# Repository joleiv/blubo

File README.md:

# BLUBO
"Blubo" is an advanced sensor for monitoring light pollution in various environments, using Hamamatsu S2386-5K photodiodes and custom transimpedance amplifiers to measure sky brightness. Essential for environmental research and crafting sustainable lighting policies.

## How to setup:

1. On a clean installation of Raspbian 11 Bullseye, install Git and download the repo:
```
git clone https://github.com/joleiv/blubo.git
```
2. After the installation is complete, you must set the file as an executable. Open terminal and run the following code:
````
cd blubo

chmod +x blubo-setup.sh

./blubo-setup.sh
````
3. Follow the instructions in the script.

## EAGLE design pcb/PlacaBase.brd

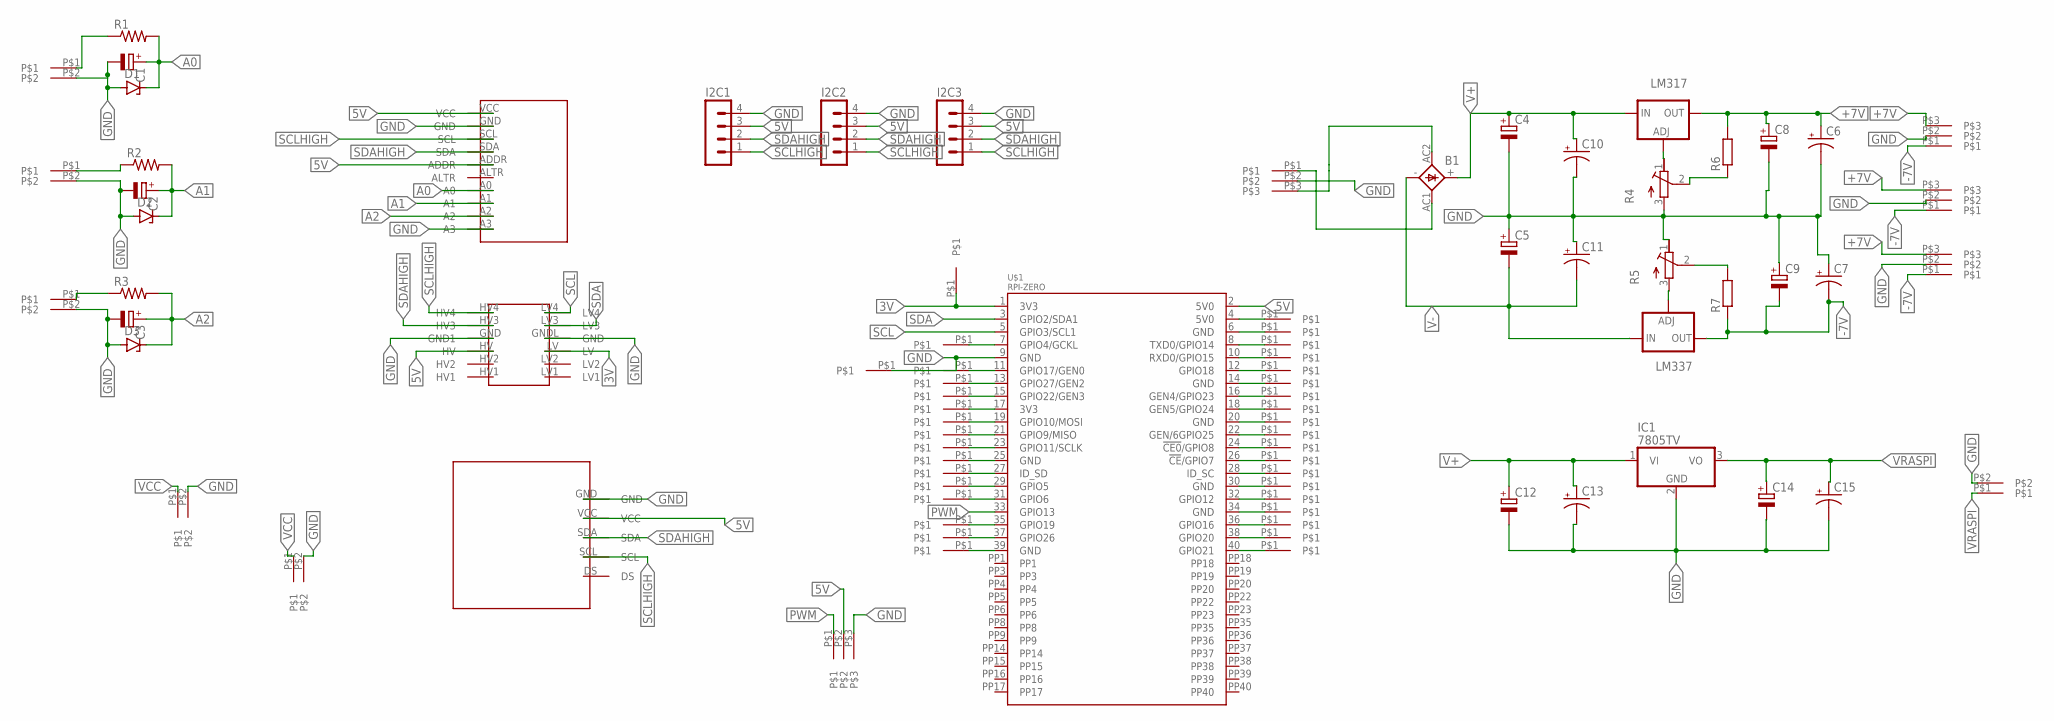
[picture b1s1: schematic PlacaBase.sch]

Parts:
5VIN: MOLEXPEQUEÑO2P
B1: KBL
C1, C2, C3: CPOL-EUE5-5; E5-5
C4, C5, C12: CPOL-EUE3.5-10; E3,5-10
C6, C7, C10, C11, C13, C15: CPOL-USTAP5-45; TAP5-45
C8, C9, C14: CPOL-EUTT2D7; TT2D7
D1, D2, D3: ZENER-DIODEDO34-7; DO34Z7
ENTRADAAC: MOLEXPEQUEÑO
I2C1, I2C2, I2C3: MA04-1
IC1: 7805TV; TO220V
LM317: LM317TS; 317TS
LM337: LM337TS; 337TS
R1, R2, R3: R-US_0204/5; 0204/5
R4, R5: R-TRIMMT93YA; RTRIMT93YA
R6, R7: R-EU_0207/7; 0207/7
U$1: RPI-ZERO; RASP_PI_ZERO_BOARD_FULL
U$2: ADS1115
U$3: RTC1307
U$4: CONVERSORLOGICO
U$5, U$13, U$14, U$15: MOLEXPEQUEÑO
U$6, U$7, U$8, U$9, U$10: MOLEXPEQUEÑO2P
U$11, U$12, U$16, U$17, U$18, U$19, U$20, U$21, U$22, U$23, U$24, U$25, U$26, U$27, U$28, U$29, U$30, U$31, U$32, U$33, U$34, U$35, U$36, U$37, U$38, U$39, U$40, U$41, U$42, U$43, U$44, U$45, U$46, U$47, U$48, U$49: PUENTE

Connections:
3V: U$1.1 (3V3), U$4.LV, U$48.P$1
3V3@2: U$1.17 (3V3), U$17.P$1
5V: I2C1.3, I2C2.3, I2C3.3, U$1.2 (5V0), U$2.ADDR, U$2.VCC, U$3.VCC, U$4.HV, U$5.P$2
5V0@2: U$1.4 (5V0), U$46.P$1
+7V: C6.+, C8.+, LM317.2 (OUT), R6.2, U$13.P$3, U$14.P$3, U$15.P$3
-7V: C7.-, C9.-, LM337.3 (OUT), R7.1, U$13.P$1, U$14.P$1, U$15.P$1
A0: C1.+, D1.C, R1.2, U$2.A0
A1: C2.+, D2.C, R2.2, U$2.A1
A2: C3.+, D3.C, R3.2, U$2.A2
AC1: B1.AC1 (AC2), ENTRADAAC.P$1
AC2: B1.AC2 (AC1), ENTRADAAC.P$3
GND: 5VIN.P$2, C1.-, C2.-, C3.-, C4.-, C5.+, C6.-, C7.+, C8.-, C9.+, C10.-, C11.+, C12.-, C13.-, C14.-, C15.-, D1.A, D2.A, D3.A, ENTRADAAC.P$2, I2C1.4, I2C2.4, I2C3.4, IC1.2 (GND), R4.3 (A), R5.1 (E), U$1.9 (GND), U$2.A3, U$2.GND, U$3.GND, U$4.GND (GND1), U$4.GNDL (GND), U$5.P$3, U$6.P$2, U$7.P$2, U$8.P$2, U$9.P$2, U$10.P$2, U$13.P$2, U$14.P$2, U$15.P$2, U$49.P$1
GND@2: U$1.25 (GND), U$21.P$1
GND@3: U$1.39 (GND), U$45.P$1
GND@4: U$1.14 (GND), U$29.P$1
GND@5: U$1.20 (GND), U$32.P$1
GND@6: U$1.30 (GND), U$37.P$1
GND@7: U$1.34 (GND), U$39.P$1
GND@8: U$1.6 (GND), U$25.P$1
unnamed: LM317.1 (ADJ), R4.1 (E)
unnamed: U$1.8 (TXD0/GPIO14), U$26.P$1
unnamed: R1.1, U$6.P$1
unnamed: R4.2 (S), R6.1
unnamed: R2.1, U$7.P$1
unnamed: U$1.10 (RXD0/GPIO15), U$27.P$1
unnamed: U$1.12 (GPIO18), U$28.P$1
unnamed: R3.1, U$8.P$1
unnamed: U$1.16 (GEN4/GPIO23), U$30.P$1
unnamed: U$1.18 (GEN5/GPIO24), U$31.P$1
unnamed: U$1.22 (GEN/6GPIO25), U$33.P$1
unnamed: U$1.24 (!CE0!/GPIO8), U$34.P$1
unnamed: LM337.1 (ADJ), R5.3 (A)
unnamed: R5.2 (S), R7.2
unnamed: U$1.26 (!CE!/GPIO7), U$35.P$1
unnamed: U$1.28 (ID_SC), U$36.P$1
unnamed: U$1.32 (GPIO12), U$38.P$1
unnamed: U$1.36 (GPIO16), U$40.P$1
unnamed: U$1.38 (GPIO20), U$41.P$1
unnamed: U$1.40 (GPIO21), U$42.P$1
unnamed: U$1.11 (GPIO17/GEN0), U$11.P$1
unnamed: U$1.13 (GPIO27/GEN2), U$12.P$1
unnamed: U$1.15 (GPIO22/GEN3), U$16.P$1
unnamed: U$1.19 (GPIO10/MOSI), U$18.P$1
unnamed: U$1.21 (GPIO9/MISO), U$19.P$1
unnamed: U$1.23 (GPIO11/SCLK), U$20.P$1
unnamed: U$1.27 (ID_SD), U$22.P$1
unnamed: U$1.29 (GPIO5), U$23.P$1
unnamed: U$1.31 (GPIO6), U$24.P$1
unnamed: U$1.35 (GPIO19), U$43.P$1
unnamed: U$1.37 (GPIO26), U$44.P$1
unnamed: U$1.7 (GPIO4/GCKL), U$47.P$1
PWM: U$1.33 (GPIO13), U$5.P$1
SCL: U$1.5 (GPIO3/SCL1), U$4.LV4
SCLHIGH: I2C1.1, I2C2.1, I2C3.1, U$2.SCL, U$3.SCL, U$4.HV4
SDA: U$1.3 (GPIO2/SDA1), U$4.LV3
SDAHIGH: I2C1.2, I2C2.2, I2C3.2, U$2.SDA, U$3.SDA, U$4.HV3
V+: B1.+, C4.+, C10.+, C12.+, C13.+, IC1.1 (VI), LM317.3 (IN)
V-: B1.-, C5.-, C11.-, LM337.2 (IN)
VCC: 5VIN.P$1, U$10.P$1
VRASPI: C14.+, C15.+, IC1.3 (VO), U$9.P$1

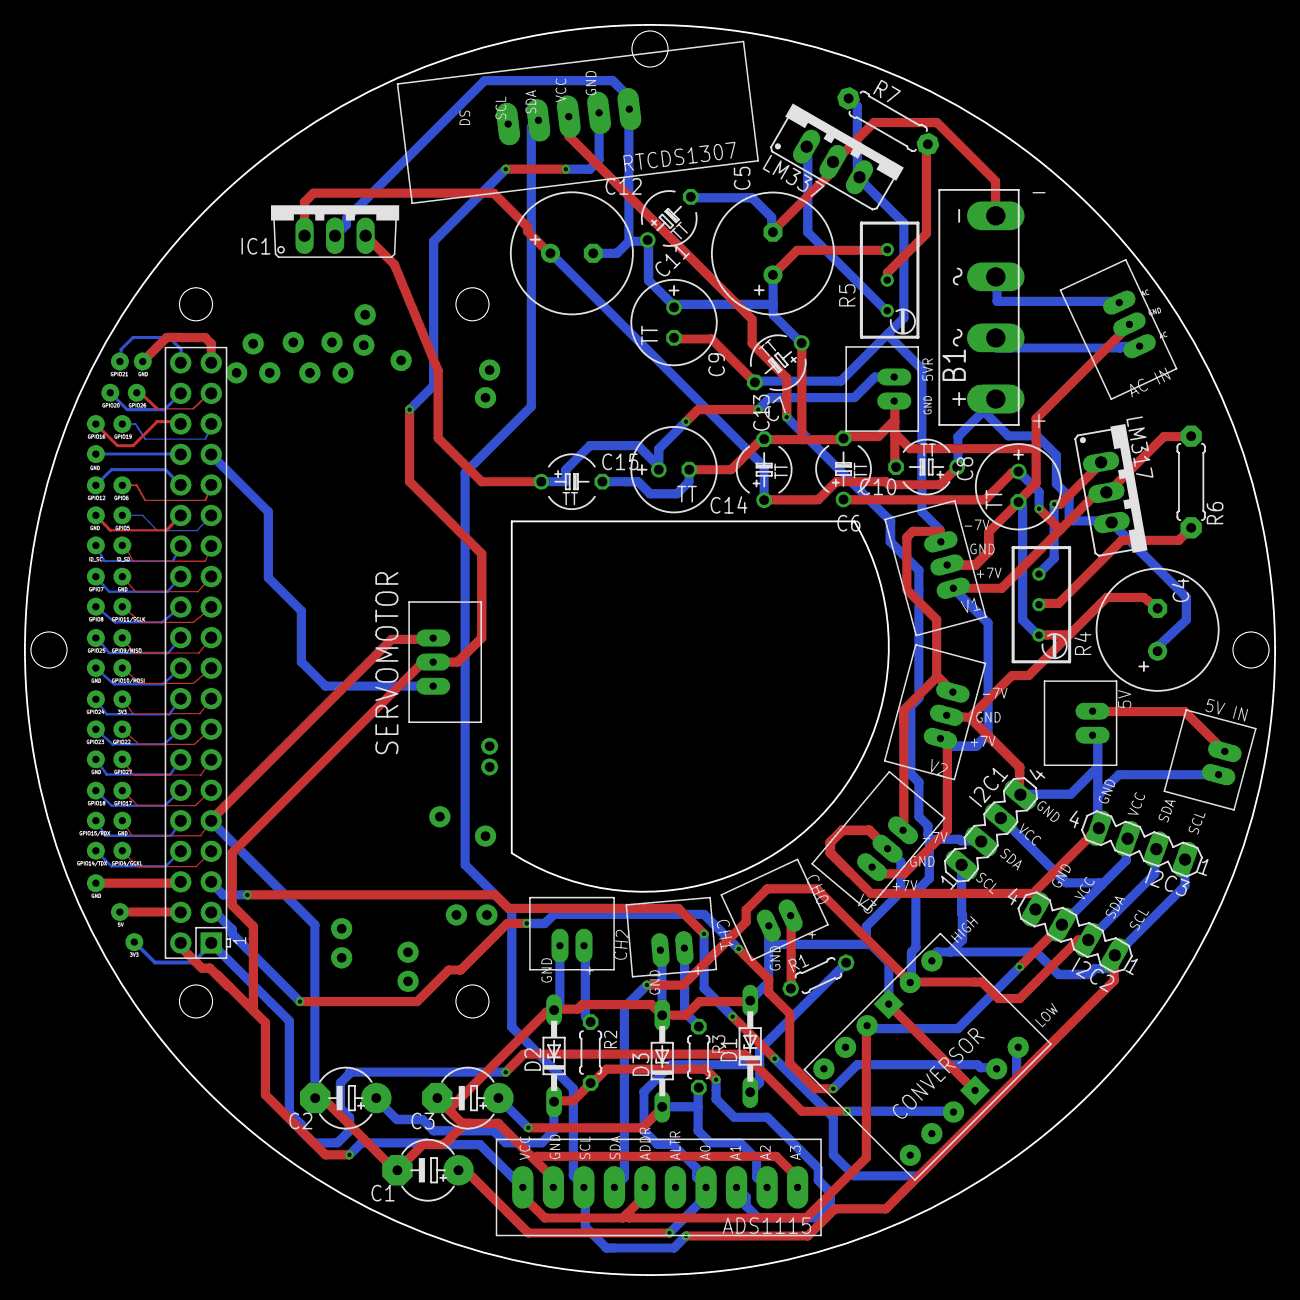
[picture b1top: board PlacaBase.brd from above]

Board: 2 copper layers, 104.0 x 104.0 mm, 83 parts (0 on the bottom side), 60 nets.

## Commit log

2024-11-14 README.md
2024-11-14 Confirmar
2024-11-14 Corrección Formato Unix
2024-12-08 Se agrega nuevo codigo - orientado a objetos
2024-12-08 Se agrega conf del RTC
2024-12-08 Codigo mejorado
2024-12-08 Se agrega ejecucion auto de main.py
2024-12-08 Se agrega rtc.py
2024-12-08 Corregido FileWriter
2024-12-08 .json actualizado
2024-12-08 Correccion Servo
2024-12-08 Corregido Angulo Servo
